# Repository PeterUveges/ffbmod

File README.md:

# YuSynth Fixed Filter Bank (modified)

This is a somewhat modified version of Yves Usson's [module](https://www.yusynth.net/Modular/EN/BANK/index.html) in Kosmo format. Changes are:

* Tuning.
* Addition of auxiliary PCB for board mounted slide pots and jacks (instead of Usson's panel mounted, wired rotary pots and jacks).
* Relocation of headers on main PCB to accommodate mating with sockets on panel components PCB. Ribbon cable is replaced by mated header/socket.
* Use of dual bypass caps (one from each rail to ground instead of one between the two rails).
* Omission of MOTM and MTA power headers.

## Errata

**WARNING!** On the first run PCBs (marked Aug 2021, no version number) the power connections to the ICs were reversed. To get around this, install all ICs "backwards", opposite the direction indicated on the silkscreen. The error has been corrected in the design files — by rerouting the power, not by turning the ICs — and power connections are correct on boards marked v1.0 (Oct 2021) or later. If in doubt use your multimeter before installing ICs to verify +12 V is on pin 4, -12 V is on pin 11. A good idea any time you build a module anyway, especially one with eight ICs!

## Tuning
Usson's filters are tuned to the same frequencies as in the Moog 914 module, except that for some reason he used 750 Hz instead of 700 Hz. The Moog filter frequencies are about six semitones (half an octave) apart. But note the following observation from the catalog description of the [Serge Resonant Equalizer](https://www.elby-designs.com/webtek/cgs/serge/cgs202/cgs202.htm): 

> Except for the top and bottom frequency bands, all other bands are spaced at an interval of a major seventh. This non-standard spacing avoids the very common effect of an accentuated resonance in one key, as will be the effect from graphic equalizers with octave or third-octave spacing between bands. Spacing by octaves will reinforce a regular overtone structure for one musical key, thereby producing regularly spaced formants accenting a particular tonality. The Resonant Equalizer's band spacing are much more interesting, producing formant peaks and valleys that are similar to those in acoustic instument sounds.

Following something like this idea, I have retuned Usson's module. Specifically, the first band pass is kept at 125 Hz and the other filters are tuned at six and a half semitones apart. 

For a list of the new frequencies, new capacitor values for the low pass and band pass filters, and new resistor values for the high pass filter, see [retuning.md](Docs/retuning.md).

In the tuning Usson used, all the required capacitances are non standard values, so he used pairs of standard value capacitors adding to the required value. Note that in this new tuning several of the required capacitances come out to available standard values. For those, only a single capacitor instead of two is used (saving 20 capacitors! Though this is partly offset by my use of dual bypass caps.) The unneeded capacitors are shown (marked DNF, "do not fit") in the schematic and have footprints on the PCB, in case I or anyone else ever wants to use this board for a differently-tuned version. For a build with my tuning, these footprints should be left unpopulated.

## Current draw
46 mA +12 V, 46 mA -12 V (This is what I measured; Usson says 70 mA on both rails (at ±15 V).)

## YuSynth request

Usson writes: 'All circuits, schematics, printed circuit board, panel design and associated data published on \[yusynth.net\] can be used for private use only.' I do not believe this repo violates his wishes and you are urged to respect them as well. CC0 licensing is intended to cover my modifications and original work, not to negate Usson's rights regarding his designs.

## Photos

## Documentation:

* [Schematic](Docs/ysFFB.pdf)
* PCB layout: [front](Docs/ysFFB_layout_front.pdf), [back](Docs/ysFFB_layout_back.pdf)
* [BOM](Docs/ysFFB_bom.md)
* [Build notes](Docs/build.md)
* [Retuning](Docs/retuning.md)

## GitHub repository

* [https://github.com/holmesrichards/ffbmod](https://github.com/holmesrichards/ffbmod)

## Submodules

This repo uses submodules aoKicad and Kosmo_panel, providing libraries needed for KiCad. To clone:

```
git clone git@github.com:holmesrichards/ffb.git
git submodule init
git submodule update
```

Alternatively do

```
git clone --recurse-submodules git@github.com:holmesrichards/ffb.git
```

Or if you download the repository as a zip file, you must also click on the "aoKicad" and "Kosmo\_panel" links on the GitHub page (they'll have "@ something" after them) and download them as separate zip files which you can unzip into this repo's aoKicad and Kosmo\_panel directories.

If desired, copy the files from aoKicad and Kosmo\_panel to wherever you prefer (your KiCad user library directory, for instance, if you have one). Then in KiCad, add symbol libraries 

```
aoKicad/ao_symbols
Kosmo_panel/Kosmo
```
and footprint libraries 
```
aoKicad/ao_tht
Kosmo_panel/Kosmo_panel.
```

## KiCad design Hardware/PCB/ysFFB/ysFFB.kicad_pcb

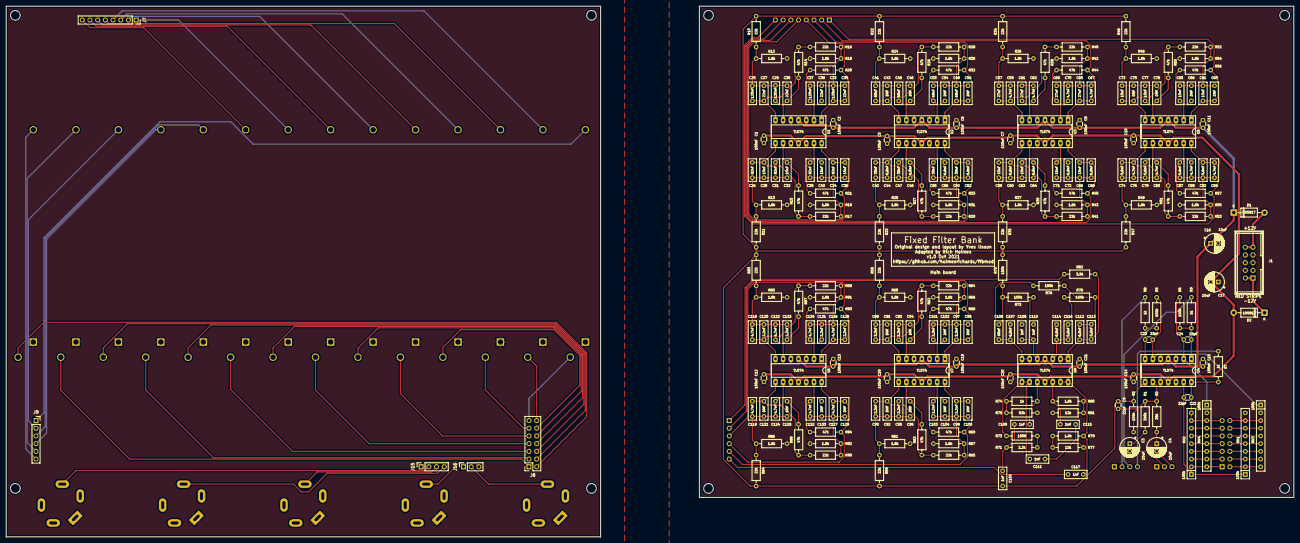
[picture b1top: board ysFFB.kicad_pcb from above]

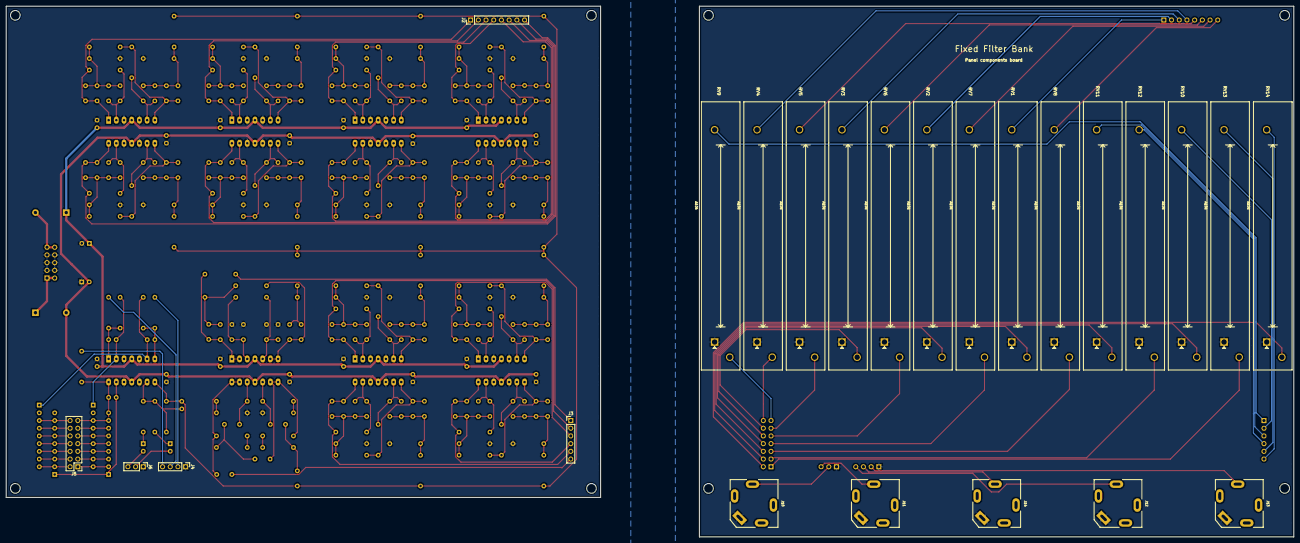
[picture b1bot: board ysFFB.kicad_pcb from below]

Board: 2 copper layers, 196.0 x 162.0 mm, 279 parts (24 on the bottom side), 158 nets.

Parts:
C1, C2, C5, C6, C7, C8, C10, C11, C12, C13, C14, C15, C18, C19, C20, C21: 100nF; C_Disc_D3.0mm_W1.6mm_P2.50mm
C3, C4, C16, C17: 10uF; CP_Radial_D6.3mm_P2.50mm
C9, C22, C23, C24: 22pF; C_Disc_D3.0mm_W1.6mm_P2.50mm
C25, C29, C33, C37: 120nF; C_Rect_L7.2mm_W2.5mm_P5.00mm_FKS2_FKP2_MKS2_MKP2
C26, C31, C34, C39: 82nF; C_Rect_L7.2mm_W2.5mm_P5.00mm_FKS2_FKP2_MKS2_MKP2
C27, C30, C35, C38: 22nF; C_Rect_L7.2mm_W2.5mm_P5.00mm_FKS2_FKP2_MKS2_MKP2
C28, C32, C36, C40, C58, C63, C66, C71, C73, C77, C81, C85: 15nF; C_Rect_L7.2mm_W2.5mm_P5.00mm_FKS2_FKP2_MKS2_MKP2
C41, C45, C49, C53, C106: 68nF; C_Rect_L7.2mm_W2.5mm_P5.00mm_FKS2_FKP2_MKS2_MKP2
C42, C47, C50, C55: 39nF; C_Rect_L7.2mm_W2.5mm_P5.00mm_FKS2_FKP2_MKS2_MKP2
C43, C46, C51, C54, C75, C78, C83, C86, C91, C92, C94, C96, C99, C100, C102, C104, C121, C125, C129, C133: DNF; C_DNF_Rect_L7.2mm_W2.5mm_P5.00mm_FKS2_FKP2_MKS2_MKP2
C44, C48, C52, C56, C60, C64, C68, C72, C107, C112, C114: 6.8nF; C_Rect_L7.2mm_W2.5mm_P5.00mm_FKS2_FKP2_MKS2_MKP2
C57, C61, C65, C69: 27nF; C_Rect_L7.2mm_W2.5mm_P5.00mm_FKS2_FKP2_MKS2_MKP2
C59, C62, C67, C70, C76, C80, C84, C88, C118, C119, C122, C124, C126, C127, C130, C132: 4.7nF; C_Rect_L7.2mm_W2.5mm_P5.00mm_FKS2_FKP2_MKS2_MKP2
C74, C79, C82, C87, C113, C116: 5.6nF; C_Rect_L7.2mm_W2.5mm_P5.00mm_FKS2_FKP2_MKS2_MKP2
C89, C93, C97, C101: 3.3nF; C_Rect_L7.2mm_W2.5mm_P5.00mm_FKS2_FKP2_MKS2_MKP2
C90, C95, C98, C103, C120, C123, C128, C131: 2.2nF; C_Rect_L7.2mm_W2.5mm_P5.00mm_FKS2_FKP2_MKS2_MKP2
C105, C108, C109, C110, C111, C115, C117: 1nF; C_Rect_L7.2mm_W2.5mm_P5.00mm_FKS2_FKP2_MKS2_MKP2
D1, D2: 1N5817; D_DO-41_SOD81_P10.16mm_Horizontal
GRAF1: Holes; ysFFB-aux-slide2_holes
H1, H2, H3, H4, H5, H6, H7, H8: MountingHole; MountingHole_3.2mm_M3
J1: Synth_power_2x5; Power_Header
J2: Conn_01x08; PinHeader_1x08_P2.54mm_Vertical
J3: Conn_01x06; PinHeader_1x06_P2.54mm_Vertical
J4: Conn_01x04; PinHeader_1x04_P2.54mm_Vertical
J5: Conn_02x07_Odd_Even; PinHeader_2x07_P2.54mm_Vertical
J6: Conn_01x03; PinHeader_1x03_P2.54mm_Vertical
J7: Conn_01x08; PinSocket_1x08_P2.54mm_Vertical
J8: Conn_02x07_Odd_Even; PinSocket_2x07_P2.54mm_Vertical
J9: Conn_01x06; PinSocket_1x06_P2.54mm_Vertical
J10, J11, J12, J13, J14: AudioJack2; Jack_6.35mm_PJ_629HAN_slots
J15: Conn_01x04; PinSocket_1x04_P2.54mm_Vertical
J16: Conn_01x03; PinSocket_1x03_P2.54mm_Vertical
R1: 390k; R_Axial_DIN0207_L6.3mm_D2.5mm_P10.16mm_Horizontal
R2: 39k; R_Axial_DIN0207_L6.3mm_D2.5mm_P10.16mm_Horizontal
R3, R5, R6: 100k; R_Axial_DIN0207_L6.3mm_D2.5mm_P10.16mm_Horizontal
R7, R8, R9, R74: 1k; R_Axial_DIN0207_L6.3mm_D2.5mm_P10.16mm_Horizontal
R10, R11, R16, R17, R22, R23, R28, R29, R34, R35, R40, R41, R46, R47, R52, R53, R58, R59, R64, R65, R83, R84, R89, R90: 22k; R_Axial_DIN0207_L6.3mm_D2.5mm_P10.16mm_Horizontal
R12, R13, R18, R19, R24, R25, R30, R31, R36, R37, R42, R43, R48, R49, R54, R55, R60, R61, R66, R67, R79, R80, R85, R86, R91, R92: 1.8k; R_Axial_DIN0207_L6.3mm_D2.5mm_P10.16mm_Horizontal
R14, R15, R20, R21, R26, R27, R32, R33, R38, R39, R44, R45, R50, R51, R56, R57, R62, R63, R68, R69, R87, R88, R93, R94: 47k; R_Axial_DIN0207_L6.3mm_D2.5mm_P10.16mm_Horizontal
R70, R72, R76, R78: 150k; R_Axial_DIN0207_L6.3mm_D2.5mm_P10.16mm_Horizontal
R71: 2.2k; R_Axial_DIN0207_L6.3mm_D2.5mm_P10.16mm_Horizontal
R73: 100R; R_Axial_DIN0207_L6.3mm_D2.5mm_P10.16mm_Horizontal
R75: 82k; R_Axial_DIN0207_L6.3mm_D2.5mm_P10.16mm_Horizontal
R77, R81: 12k; R_Axial_DIN0207_L6.3mm_D2.5mm_P10.16mm_Horizontal
R82: 3.9k; R_Axial_DIN0207_L6.3mm_D2.5mm_P10.16mm_Horizontal
RN1, RN2, RN3, RN4: 100k; R_Array_SIP9
RV1, RV2, RV3, RV4, RV5, RV6, RV7, RV8, RV9, RV10, RV11, RV12, RV13, RV14: A10k; Potentiometer_Alpha_RA6020F_Single_Slide
U1, U2, U3, U4, U5, U6, U7, U8: TL074; DIP-14_W7.62mm_Socket_LongPads

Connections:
+12V: C2.2, C6.2, C8.2, C11.2, C13.2, C15.2, C16.1, C19.2, C21.2, D1.1, U1.4, U2.4, U3.4, U4.4, U5.4, U6.4, U7.4, U8.4
-12V: C1.1, C5.1, C7.1, C10.1, C12.1, C14.1, C17.2, C18.1, C20.1, D2.2, U1.11, U2.11, U3.11, U4.11, U5.11, U6.11, U7.11, U8.11
/+12_IN: D1.2, J1.9, J1.10
/-12_IN: D2.1, J1.1, J1.2
/Band pass 1, 2/IN: C9.1, C105.2, R3.1, R10.2, R11.2, R22.2, R23.2, R34.2, R35.2, R46.2, R47.2, R58.2, R59.2, R70.2, R83.2, R84.2, U4.8
/Panel components/BP1PP: J7.4, RV4.3
/Panel components/BP2PP: J7.5, RV5.3
/Panel components/BP3PP: J7.3, RV3.3
/Panel components/BP4PP: J7.6, RV6.3
/Panel components/BP5PP: J7.2, RV2.3
/Panel components/BP6PP: J7.7, RV7.3
/Panel components/BP7PP: J7.1, RV1.3
/Panel components/BP8PP: J7.8, RV8.3
/Panel components/BP9PP: J9.3, RV11.3
/Panel components/BP10PP: J9.4, RV12.3
/Panel components/BP11PP: J9.2, RV10.3
/Panel components/BP12P: J9.5, RV13.3
/Panel components/HPPP: J9.6, RV14.3
/Panel components/LPP: J9.1, RV9.3
ALL: J4.4, R7.1
ALL_P: J12.T, J15.4
BP1P: C33.1, C35.1, J2.4, R20.1, U1.1
BP2P: C34.1, C36.1, J2.5, R21.1, U1.14
BP3P: C49.1, C51.1, J2.3, R32.1, U2.1
BP4P: C50.1, C52.1, J2.6, R33.1, U2.14
BP5P: C65.1, C67.1, J2.2, R44.1, U3.1
BP6P: C66.1, C68.1, J2.7, R45.1, U3.14
BP7P: C81.1, C83.1, J2.1, R56.1, U5.1
BP8P: C82.1, C84.1, J2.8, R57.1, U5.14
BP9P: C126.1, C128.1, J3.3, R93.1, U6.1
BP10P: C127.1, C129.1, J3.4, R94.1, U6.14
BP11P: C97.1, C99.1, J3.2, R68.1, U7.1
BP12P: C98.1, C100.1, J3.5, R69.1, U7.14
EVEN: J4.3, R9.1
EVEN_1: J5.1, RN2.2, RN4.9
EVEN_2: J5.3, RN2.3, RN4.8
EVEN_3: J5.5, RN2.4, RN4.7
EVEN_4: J5.7, RN2.5, RN4.6
EVEN_5: J5.9, RN2.6, RN4.5
EVEN_6: J5.11, RN2.7, RN4.4
EVEN_7: J5.13, RN2.8, RN4.3
EVEN_P: J14.T, J15.3
GND: C1.2, C2.1, C5.2, C6.1, C7.2, C8.1, C10.2, C11.1, C12.2, C13.1, C14.2, C15.1, C16.2, C17.1, C18.2, C19.1, C20.2, C21.1, C108.2, C110.2, C114.2, C116.2, J1.3, J1.4, J1.5, J1.6, J1.7, J1.8, J4.1, J6.1, R12.2, R13.2, R18.2, R19.2, R24.2, R25.2, R30.2, R31.2, R36.2, R37.2, R42.2, R43.2, R48.2, R49.2, R54.2, R55.2, R60.2, R61.2, R66.2, R67.2, R75.2, R81.2, R85.2, R86.2, R91.2, R92.2, U1.3, U1.5, U1.10, U1.12, U2.3, U2.5, U2.10, U2.12, U3.3, U3.5, U3.10, U3.12, U4.3, U4.5, U4.10, U4.12, U5.3, U5.5, U5.10, U5.12, U6.3, U6.5, U6.10, U6.12, U7.3, U7.5, U7.10, U7.12
GND1: J10.S, J11.S, J12.S, J13.S, J14.S, J15.1, J16.1, RV1.1, RV2.1, RV3.1, RV4.1, RV5.1, RV6.1, RV7.1, RV8.1, RV9.1, RV10.1, RV11.1, RV12.1, RV13.1, RV14.1
HIGH_INPUT: C3.2, J6.2
HIGH_INPUT_P: J10.T, J16.2
HPP: C117.1, J3.6
LOW_INPUT: C4.2, J6.3
LOW_INPUT_P: J11.T, J16.3
LPP: J3.1, R82.1
unnamed: C3.1, R1.2
unnamed: C4.1, R2.2
unnamed: C9.2, R1.1, R2.1, R3.2, U4.9
unnamed: C22.1, R7.2, RN2.9, U4.14
unnamed: C22.2, RN1.1, RN2.1, U4.13
unnamed: C23.1, R5.1, R8.2, U4.7
unnamed: C23.2, R5.2, RN3.1, U4.6
unnamed: C24.1, R6.1, R9.2, U4.1
unnamed: C24.2, R6.2, RN4.1, U4.2
unnamed: C25.1, C27.1, R14.1, R16.2, U1.7
unnamed: C25.2, C27.2, C29.2, C30.2, R10.1, R12.1
unnamed: C26.1, C28.1, R15.1, R17.2, U1.8
unnamed: C26.2, C28.2, C31.2, C32.2, R11.1, R13.1
unnamed: C29.1, C30.1, R14.2, U1.6
unnamed: C31.1, C32.1, R15.2, U1.9
unnamed: C33.2, C35.2, C37.2, C38.2, R16.1, R18.1
unnamed: C34.2, C36.2, C39.2, C40.2, R17.1, R19.1
unnamed: C37.1, C38.1, R20.2, U1.2
unnamed: C39.1, C40.1, R21.2, U1.13
unnamed: C41.1, C43.1, R26.1, R28.2, U2.7
unnamed: C41.2, C43.2, C45.2, C46.2, R22.1, R24.1
unnamed: C42.1, C44.1, R27.1, R29.2, U2.8
unnamed: C42.2, C44.2, C47.2, C48.2, R23.1, R25.1
unnamed: C45.1, C46.1, R26.2, U2.6
unnamed: C47.1, C48.1, R27.2, U2.9
unnamed: C49.2, C51.2, C53.2, C54.2, R28.1, R30.1
unnamed: C50.2, C52.2, C55.2, C56.2, R29.1, R31.1
unnamed: C53.1, C54.1, R32.2, U2.2
unnamed: C55.1, C56.1, R33.2, U2.13
unnamed: C57.1, C59.1, R38.1, R40.2, U3.7
unnamed: C57.2, C59.2, C61.2, C62.2, R34.1, R36.1
unnamed: C58.1, C60.1, R39.1, R41.2, U3.8
unnamed: C58.2, C60.2, C63.2, C64.2, R35.1, R37.1
unnamed: C61.1, C62.1, R38.2, U3.6
unnamed: C63.1, C64.1, R39.2, U3.9
unnamed: C65.2, C67.2, C69.2, C70.2, R40.1, R42.1
unnamed: C66.2, C68.2, C71.2, C72.2, R41.1, R43.1
unnamed: C69.1, C70.1, R44.2, U3.2
unnamed: C71.1, C72.1, R45.2, U3.13
unnamed: C73.1, C75.1, R50.1, R52.2, U5.7
unnamed: C73.2, C75.2, C77.2, C78.2, R46.1, R48.1
unnamed: C74.1, C76.1, R51.1, R53.2, U5.8
unnamed: C74.2, C76.2, C79.2, C80.2, R47.1, R49.1
unnamed: C77.1, C78.1, R50.2, U5.6
unnamed: C79.1, C80.1, R51.2, U5.9
unnamed: C81.2, C83.2, C85.2, C86.2, R52.1, R54.1
unnamed: C82.2, C84.2, C87.2, C88.2, R53.1, R55.1
unnamed: C85.1, C86.1, R56.2, U5.2
unnamed: C87.1, C88.1, R57.2, U5.13
unnamed: C89.1, C91.1, R62.1, R64.2, U7.7
unnamed: C89.2, C91.2, C93.2, C94.2, R58.1, R60.1
unnamed: C90.1, C92.1, R63.1, R65.2, U7.8
unnamed: C90.2, C92.2, C95.2, C96.2, R59.1, R61.1
unnamed: C93.1, C94.1, R62.2, U7.6
unnamed: C95.1, C96.1, R63.2, U7.9
unnamed: C98.2, C100.2, C103.2, C104.2, R65.1, R67.1
unnamed: C101.1, C102.1, R68.2, U7.2
unnamed: C97.2, C99.2, C101.2, C102.2, R64.1, R66.1
unnamed: C103.1, C104.1, R69.2, U7.13
unnamed: C105.1, C109.2, R71.2
unnamed: C106.1, C107.1, R76.2, U8.6, U8.7
unnamed: C106.2, C107.2, R70.1, R72.2
unnamed: C108.1, C110.1, R72.1, U8.5
unnamed: C109.1, R74.1, U8.10
unnamed: C111.1, C115.2, R77.2
unnamed: C111.2, R73.1, U8.8, U8.9
unnamed: C112.1, C113.1, R82.2, U8.1, U8.2
unnamed: C112.2, C113.2, R76.1, R78.2
unnamed: C114.1, C116.1, R78.1, U8.3
unnamed: C115.1, R80.1, U8.12
unnamed: C117.2, R79.1, U8.13, U8.14
unnamed: C118.1, C120.1, R87.1, R89.2, U6.7
unnamed: C118.2, C120.2, C122.2, C123.2, R83.1, R85.1
unnamed: C119.1, C121.1, R88.1, R90.2, U6.8
unnamed: C119.2, C121.2, C124.2, C125.2, R84.1, R86.1
unnamed: C122.1, C123.1, R87.2, U6.6
unnamed: C124.1, C125.1, R88.2, U6.9
unnamed: C126.2, C128.2, C130.2, C131.2, R89.1, R91.1
unnamed: C127.2, C129.2, C132.2, C133.2, R90.1, R92.1
unnamed: C130.1, C131.1, R93.2, U6.2
unnamed: C132.1, C133.1, R94.2, U6.13
unnamed: R71.1, R73.2
unnamed: R74.2, R75.1
unnamed: R77.1, R79.2
unnamed: R80.2, R81.1
ODD: J4.2, R8.1
ODD_1: J5.2, RN1.2, RN3.9
ODD_2: J5.4, RN1.3, RN3.8
ODD_3: J5.6, RN1.4, RN3.7
ODD_4: J5.8, RN1.5, RN3.6
ODD_5: J5.10, RN1.6, RN3.5
ODD_6: J5.12, RN1.7, RN3.4
ODD_7: J5.14, RN1.8, RN3.3
ODD_P: J13.T, J15.2
P2_1: J8.14, RV4.2
P2_2: J8.11, RV5.2
P2_3: J8.12, RV3.2
P2_4: J8.9, RV6.2
P2_5: J8.10, RV2.2
P2_6: J8.7, RV7.2
P2_7: J8.8, RV1.2
P2_8: J8.5, RV8.2
P2_9: J8.6, RV11.2
P2_10: J8.3, RV12.2
P2_11: J8.4, RV10.2
P2_12: J8.1, RV13.2
P2_H: J8.2, RV14.2
P2_L: J8.13, RV9.2

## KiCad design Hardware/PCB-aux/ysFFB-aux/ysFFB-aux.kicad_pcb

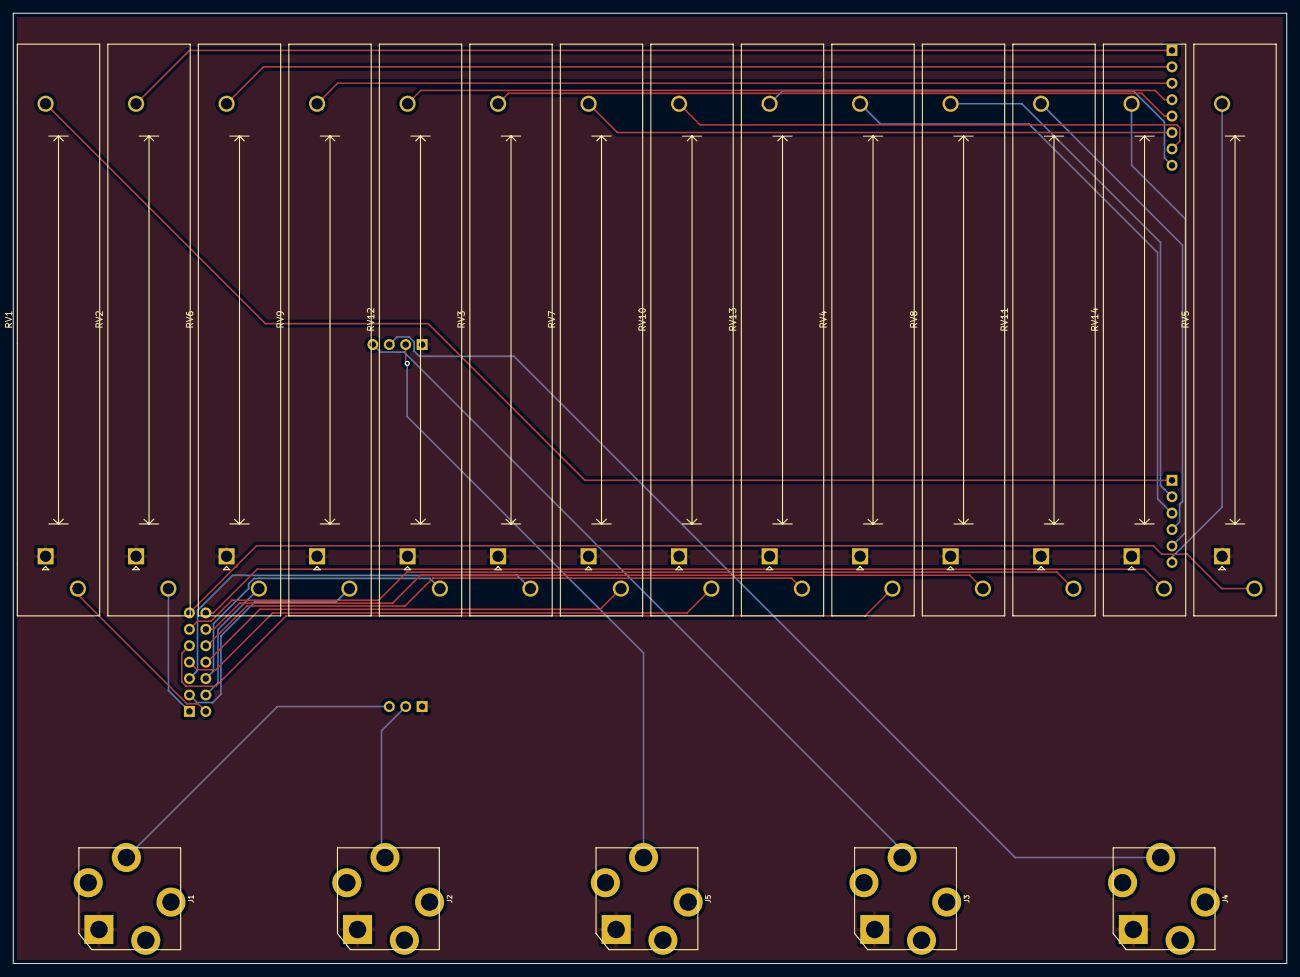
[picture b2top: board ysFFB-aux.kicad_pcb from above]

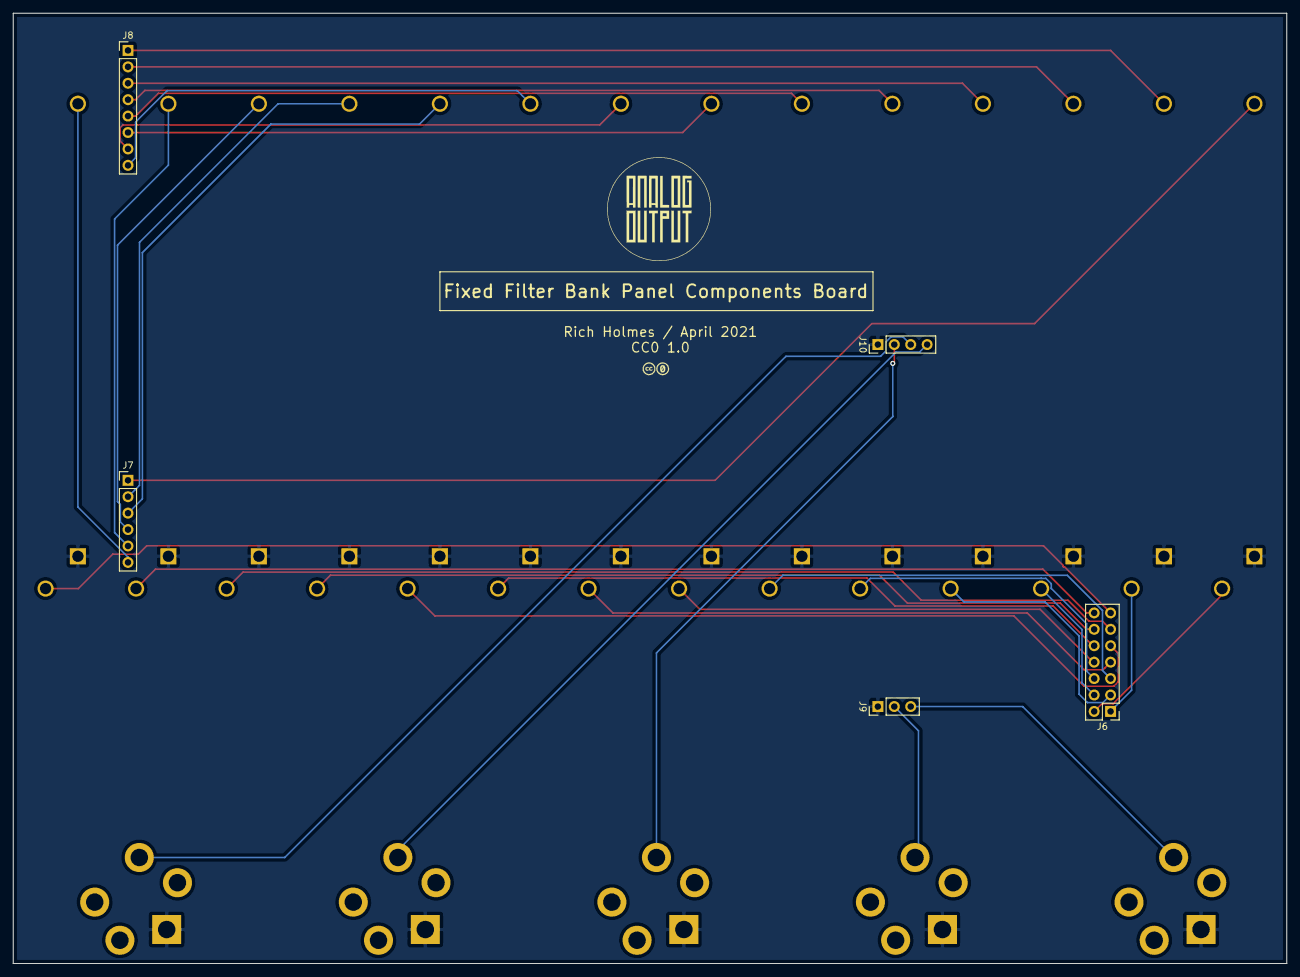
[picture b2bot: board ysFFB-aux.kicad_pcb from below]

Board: 2 copper layers, 197.0 x 147.0 mm, 27 parts (7 on the bottom side), 34 nets.

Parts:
GRAF1: Holes and main PCB; ysFFB-aux-slide2_holes-mainpcba
GRAF2: AO logo; analogoutput
GRAF3: CC0 logo; CC0_logo
J1, J2, J3, J4, J5: AudioJack2; Jack_6.35mm_PJ_629HAN
J6: Conn_02x07_Odd_Even; PinHeader_2x07_P2.54mm_Vertical
J7: Conn_01x06; PinHeader_1x06_P2.54mm_Vertical
J8: Conn_01x08; PinHeader_1x08_P2.54mm_Vertical
J9: Conn_01x03; PinHeader_1x03_P2.54mm_Vertical
J10: Conn_01x04; PinHeader_1x04_P2.54mm_Vertical
RV1, RV2, RV3, RV4, RV5, RV6, RV7, RV8, RV9, RV10, RV11, RV12, RV13, RV14: A10k; Potentiometer_Alpha_RA6020F_Single_Slide

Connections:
BP_01_CW: J8.1, RV2.3
BP_01_W: J6.1, RV2.2
BP_02_CW: J8.2, RV6.3
BP_02_W: J6.4, RV6.2
BP_03_CW: J8.3, RV9.3
BP_03_W: J6.3, RV9.2
BP_04_CW: J8.4, RV12.3
BP_04_W: J6.6, RV12.2
BP_05_CW: J8.5, RV3.3
BP_05_W: J6.5, RV3.2
BP_06_CW: J8.6, RV7.3
BP_06_W: J6.8, RV7.2
BP_07_CW: J8.7, RV10.3
BP_07_W: J6.7, RV10.2
BP_08_CW: J8.8, RV13.3
BP_08_W: J6.10, RV13.2
BP_09_CW: J7.3, RV4.3
BP_09_W: J6.9, RV4.2
BP_10_CW: J7.2, RV8.3
BP_10_W: J6.12, RV8.2
BP_11_CW: J7.4, RV11.3
BP_11_W: J6.11, RV11.2
BP_12_CW: J7.5, RV14.3
BP_12_W: J6.14, RV14.2
GND: J1.S, J2.S, J3.S, J4.S, J5.S, J9.1, J10.1, RV1.1, RV2.1, RV3.1, RV4.1, RV5.1, RV6.1, RV7.1, RV8.1, RV9.1, RV10.1, RV11.1, RV12.1, RV13.1, RV14.1
HP_CW: J7.6, RV5.3
HP_W: J6.13, RV5.2
JACK_EVEN: J4.T, J10.3
JACK_HI: J2.T, J9.2
JACK_LO: J1.T, J9.3
JACK_ODD: J5.T, J10.2
JACK_TOTAL: J3.T, J10.4
LP_CW: J7.1, RV1.3
LP_W: J6.2, RV1.2

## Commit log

2021-05-26 Initial version
2021-07-29 New slide pot layout
2021-08-07 Kosmo_panel lib update
2021-08-11 Reorganized; new main board design; replaced aux board design
2021-08-12 Fix socket that looked suspiciously like a header. Fix every last remaining inconsistency.
2021-08-12 submodules
2021-08-19 Revised NPTH scheme
2021-08-20 No NPTH specialization
2021-08-21 relocate libraries; PCB revisions
2021-08-21 rm project libraries
2021-08-27 submodule doc
2021-09-09 Clean up libraries, Schottky footprint update
2021-09-15 SVG decontamination
2021-09-15 Tidy C values and symbols
2021-09-18 Cap vals on PCB, revised panel
2021-09-19 Gerbers
2021-09-23 Pre fab tweaks, new Gerbers, correct alignment and make PCB dimensions symmetric in module
2021-10-17 Minor sch tweaks, revise README and break out retuning doc
2021-10-17 Fix and document power connection error
2021-10-22 YuSynth request
2021-10-22 Create LICENSE
2021-10-23 It's tested
2021-10-23 Documentation, rm unneeded images, add needed images, move script to Software folder
2021-10-23 rm stray space
2021-10-23 More on Usson's wishes
2021-10-23 Still more on Usson's wishes
2021-10-23 Photos
2021-10-23 Format
2021-10-24 Correct Gerbers
2021-10-24 Minor clarification
2021-10-24 113 actually
2021-12-24 Current draw
